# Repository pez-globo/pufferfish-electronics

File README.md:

# vent-pcb

Electronic hardware board layout files for the Pufferfish ventilator.

The schematic and PCB files for this project can be viewed online at [CADLAB.io](https://cadlab.io/project/22897).

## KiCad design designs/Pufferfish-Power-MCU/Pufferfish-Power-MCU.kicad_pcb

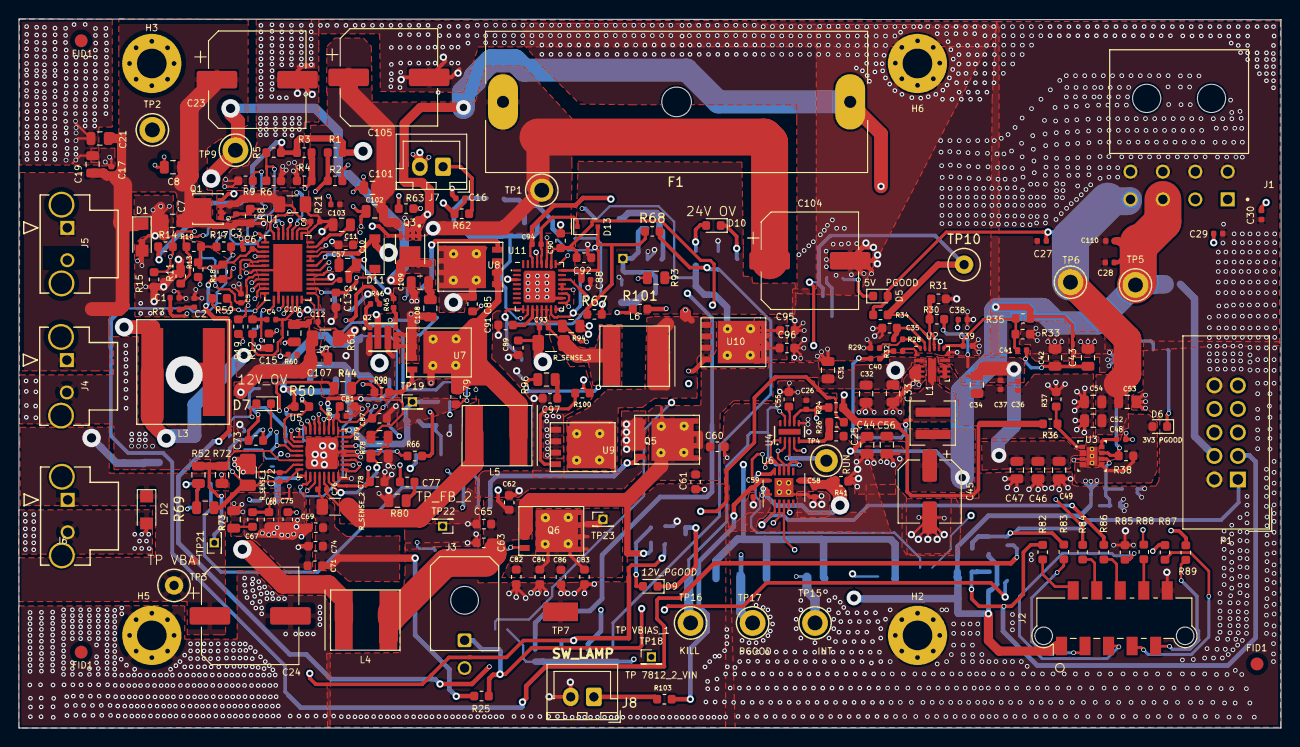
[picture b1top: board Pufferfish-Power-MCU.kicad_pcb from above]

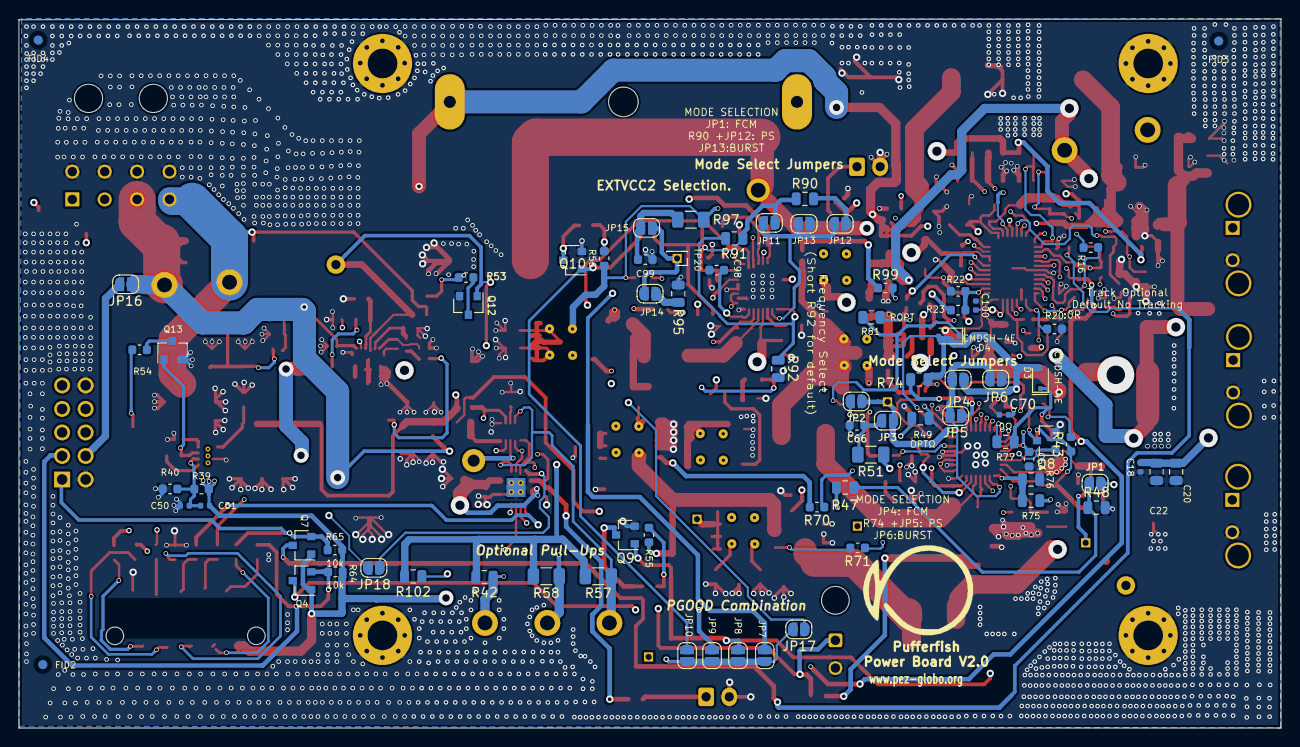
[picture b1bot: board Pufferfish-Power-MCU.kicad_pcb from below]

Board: 4 copper layers, 136.3 x 76.6 mm, 311 parts (77 on the bottom side), 148 nets.

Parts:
C1, C3, C16, C100: CAP_NC_0402; CAP_SMD_0402
C2, C26: CAP_10nF_50V_X7R_0402; CAP_SMD_0402
C4, C6, C17, C18, C27, C28, C29, C30, C36, C37, C40, C103, C110: CAP_100nF_50V_X7R_0402; CAP_SMD_0402
C5, C41, C51: CAP_100pF_10V_NP0_0402; CAP_SMD_0402
C7, C8, C19, C20, C21, C22, C34, C57, C101, C102, C106, C107, C108, C109: CAP_10uF_35V_X5R_0805; CAP_SMD_0805
C9, C12, C39, C50, C70, C72, C76, C88, C93, C94: CAP_1nF_50V_C0G_0402; CAP_SMD_0402
C10: CAP_1uF_35V_X7R_0603; CAP_SMD_0603
C11: CAP_330nF_35V_X7R_0805; CAP_SMD_0805
C13: CAP_470nF_35V_X7R_0603; CAP_SMD_0603
C14: CAP_2.2uF_10V_X7S_0402; CAP_SMD_0402
C15: CAP_330nF_16V_X7R_0603; CAP_SMD_0603
C23, C24, C104, C105: CAP_AE_SMD_220uF_25V_8mm; CP_Elec_10x7.9
C25, C64, C66, C75, C91: 0.1uF; CAP_SMD_0603
C31, C32, C33, C42, C43, C44, C46, C47, C49, C52, C53, C54, C56: CAP_22uF_25V_X5R_0805; CAP_SMD_0805
C35: CAP_4.7uF_16V_X6S_0603; CAP_SMD_0603
C38: CAP_47nF_50V_X7R_0402; CAP_SMD_0402
C45: CAP_AE_SMD_100uF_10V_6mm; CP_Elec_6.3x5.4
C48: CAP_3.3nF_50V_X7R_0402; CAP_SMD_0402
C55: 5.6u; CAP_SMD_0603
C58, C59: 0.1u; CAP_SMD_0402
C60: 150uF; CAP_SMD_0603
C61: 100uF; CAP_SMD_0603
C62: 4.7uF; CAP_SMD_0603
C63, C65: C_OPT; CAP_SMD_0603
C67: 2.2n; CAP_SMD_0603
C68: 68p; CAP_SMD_0603
C69: 33u; CAP_SMD_0603
C71, C74, C84, C85: 10u; CAP_SMD_0603
C73: 0.1u; CAP_SMD_0603
C77: 10n; CAP_SMD_0603
C78: 1n; CAP_SMD_0603
C79: 1nF; CAP_SMD_0603
C80: 0.1uF; CAP_SMD_0402
C81, C82, C92: OPT_CAP; CAP_SMD_0603
C83: 4.7u; CAP_SMD_0603
C86: 100u; CAP_SMD_0603
C87: 1u; CAP_SMD_0603
C89: 33uF; CAP_SMD_0603
C90: 10uF; CAP_SMD_0603
C95, C96, C97, C98, C99: CAP_SMD_0603
D1: TVS_24V_SOD123FL-2; D_SOD-123F
D2: TVS_15V_SOD123FL-2; D_SOD-123F
D3, D4, D13: CMDSH-4E; D_SOD-323F
D5, D6: LED_SMD_0603_ORANGE; LED_0603_1608Metric
D7, D9, D10: LED_SMD_0603_GREEN; LED_0603_1608Metric
D11: 1N4448HLP; D_SOD-123
F1: Fuse; Fuseholder_Cylinder-6.3x32mm_Schurter_0031-8002_Horizontal_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
FID1, FID1#2, FID1#3, FID2, FID3, FID4: Fiducial; Fiducial_1mm_Mask2mm
H2, H3, H5, H6: STANDOFF_ELECTRICAL; MountingHole_3.2mm_M3_Pad_Via
J1: 172316-1108; MOLEX_172316-1108
J2: 90814-0010; Molex_Picoflex_90814-0010_2x05_P1.27mm_Vertical
J3: 0430450200; Molex_Micro-Fit_3.0_43045-0200_2x01_P3.00mm_Horizontal
J4, J5, J6: CON_1722871202_MOL; UL_1722871202
J7: B2B-XH-A(LF)(SN); JST_XH_B2B-XH-A_1x02_P2.50mm_Vertical
J8: LAMP CONN; JST_XH_B2B-XH-A_1x02_P2.50mm_Vertical
JP1: SolderJumper_TRACKING; SolderJumper-2_P1.3mm_Open_RoundedPad1.0x1.5mm
JP2, JP14: SolderJumper_EXTMODE1; SolderJumper-2_P1.3mm_Open_RoundedPad1.0x1.5mm
JP3, JP15: SolderJumper_EXTMODE2; SolderJumper-2_P1.3mm_Open_RoundedPad1.0x1.5mm
JP4, JP11: SolderJumper_FCM; SolderJumper-2_P1.3mm_Open_RoundedPad1.0x1.5mm
JP5, JP12: SolderJumper_PS; SolderJumper-2_P1.3mm_Open_RoundedPad1.0x1.5mm
JP6, JP13: SolderJumper_Burst; SolderJumper-2_P1.3mm_Open_RoundedPad1.0x1.5mm
JP7, JP8, JP9, JP10, JP17, JP18: SolderJumper_PGOOD; SolderJumper-2_P1.3mm_Open_RoundedPad1.0x1.5mm
JP16: OPT_5V; SolderJumper-2_P1.3mm_Open_RoundedPad1.0x1.5mm
L1: PM2201.122NLT; L_Pulse_PA5001
L2: LOGO_PUFFERFISH
L3: XAL1010-103MEB; XAL1010
L4: 4.7u; L_Coilcraft_XxL7070
L5: 1.0u; L_Coilcraft_XxL7070
L6: 15uH; L_Coilcraft_XxL7070
P1: Aardvark Conn 10 P IDC; IDC-Header_2x05_P2.54mm_Vertical
Q1: FDMC8327L; TRANS_FDMC8327L
Q2: FDMC8030; TRANS_FDMC8030
Q3: SI7611DN-T1-GE3; VISHAY_SIS468DN-T1-GE3
Q4, Q7, Q8, Q9, Q10, Q12, Q13: 2N7002E; SOT-23
Q5, Q6: Q_NMOS_BSC093N04LSG; PG-TDSON-8
R1, R2, R4, R5, R9, R10, R11, R14, R15, R23: RES_0603_NC; RES_SMD_0603
R3, R6, R8, R13, R16, R17, R18, R20, R22, R31, R33, R34, R37, R38, R40, R59, R62: RES_10K_0603_SMD; RES_SMD_0603
R7, R32, R45, R46, R60: RES_0R_0402_SMD; RES_SMD_0402
R12: RES_301K_0603_SMD; RES_SMD_0603
R19: RES_100K_0603_SMD; RES_SMD_0603
R21, R61: CSNL1206FT3L00; RES_SMD_1206
R24: 1k; RES_SMD_0603
R25, R41, R64, R65: 10k; RES_SMD_0603
R26: 5.1k; RES_SMD_0603
R28: RES_62K_0402_SMD; RES_SMD_0402
R29: RES_51K_0402_SMD; RES_SMD_0402
R30: RES_47K_0603_SMD; RES_SMD_0603
R35, R36: RES_73K2_0603_SMD; RES_SMD_0603
R39: RES_31K6_0603_SMD; RES_SMD_0603
R42, R102: RPULL_OPT; RES_SMD_0805
R43, R55: 510R; RES_SMD_0603
R44, R69, R77: 0Ω; RES_SMD_0805
R47, R48, R49, R75, R76, R91, R92, R95: OPTΩ; RES_SMD_0805
R50, R66, R67, R68: 1M; RES_SMD_0603
R51, R97: OPTΩ; RES_SMD_1206
R52: 499k; RES_SMD_0805
R53: RES_330R_0603_SMD; RES_SMD_0603
R54: 330R; RES_SMD_0603
R56: 1.2k; RES_SMD_0603
R57, R58: RPULL_OPT; RES_SMD_1206
R63: RES_20K_0603_SMD; RES_SMD_0603
R70, R71, R82, R83, R84, R85, R86, R87, R88, R89, R98, R99, R100, R101: 0Ω; RES_SMD_0603
R72: 35.7k; RES_SMD_0805
R73: 15k; RES_SMD_0805
R74, R90: 100k OPT; RES_SMD_0805
R78: 49.9k; RES_SMD_0805
R79: 549K; RES_SMD_0805
R80: 3.6k; RES_SMD_0805
R81: ROPT; RES_SMD_0805
R93: 549k; RES_SMD_0805
R94: 28.7k; RES_SMD_0805
R96: 53.6k; RES_SMD_0805
R103: 150 Ω; RES_SMD_0603
R_SENSE_1: 0.003; RES_SMD_1206
R_SENSE_2: 0.004; RES_SMD_1206
R_SENSE_3: 0.015; RES_SMD_1206
TP1, TP2, TP3, TP4, TP5, TP6, TP9, TP15, TP16, TP17: TP_TH_KEYSTONE_5010; TestPoint_Keystone_5010-5014_Multipurpose
TP7: TP_SMT_KEYSTONE_5019; TP380X203
TP10: TP_PGOOD_5V; TestPoint_Keystone_5005-5009_Compact
TP18: TP_VOUT_12V; PinHeader_1x01_P1.27mm_Vertical
TP19: TP_EXTVCC1; PinHeader_1x01_P1.27mm_Vertical
TP20: TP_EXTVCC2; PinHeader_1x01_P1.27mm_Vertical
TP21: TP_VFB_1_1; PinHeader_1x01_P1.27mm_Vertical
TP22: TP_VFB_2_1; PinHeader_1x01_P1.27mm_Vertical
TP23: TP_VBIAS_1; PinHeader_1x01_P1.27mm_Vertical
U1: LTC4015EUHF#PBF; QFN50P700X500X80-39N
U2: TPS568215RNN; Texas_RNN0018A
U3: TPS82130; TPS82130SILR
U4: LTC2955; DFN-10-1EP_2x3mm_P0.5mm_EP0.64x2.4mm
U5: LTC7812; QFN-32-1EP_5x5mm_P0.5mm_EP3.45x3.45mm
U6: TXS0104ERGYR; Texas_S-PVQFN-N14_ThermalVias
U7, U8, U9, U10: BSC027N04LSG; PG-TDSON-8
U11: LTC7812-LTC7812; QFN-32-1EP_5x5mm_P0.5mm_EP3.45x3.45mm

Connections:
3V3-PGOOD: JP18.2, Q13.1, R38.2, U3.7
/3.3V Buck/3V3-EN: R36.2, R37.1, U3.1
/3.3V Buck/3V3-FB: C50.1, C51.2, R39.2, R40.1, U3.6
/3.3V Buck/3V3-SS: C48.1, U3.8
/5V Buck/5V-BUCK-BOOT: R32.1, U2.1
/5V Buck/5V-BUCK-SW: C40.1, L1.1, U2.6, U2.7
/5V Buck/5V-EN: R30.2, R31.1, U2.15
/5V Buck/5V-FB: C39.1, C41.2, R33.1, R35.2, U2.13
/5V Buck/5V-MODE: R28.2, R29.1, U2.18
/5V Buck/5V-SS: C38.1, U2.14
/LTC2955/INT_LVL: R42.1, TP15.1, U4.1, U6.12
/LTC2955/KILL_LVL: R57.1, TP16.1, U4.9, U6.10
/LTC2955/PG_LVL: R58.1, TP17.1, U4.2, U6.11
/LTC4015/PP-BATSENS: C100.1, R60.2, U1.18
/LTC4015/PP-BG: R45.2, U1.26
/LTC4015/PP-BOOST: C13.1, D11.1, U1.25
/LTC4015/PP-BOT-GATE: Q2.8, R45.1
/LTC4015/PP-CCREFM: C4.2, R12.2, U1.16
/LTC4015/PP-CCREFP: C4.1, R12.1, U1.17
/LTC4015/PP-CELL0: R1.1, R2.2, U1.38
/LTC4015/PP-CELL1: R3.2, R4.2, U1.1
/LTC4015/PP-CELL2: R5.1, R6.1, U1.2
/LTC4015/PP-CHEM0: R10.1, R11.2, U1.36
/LTC4015/PP-CHEM1: R14.1, R15.2, U1.37
/LTC4015/PP-CSP: C12.1, C15.1, C108.1, C109.1, L3.2, Q3.5, Q3.6, Q3.7, Q3.8, Q3.9, R61.1, TP9.1, U1.20
/LTC4015/PP-CSPM5: C15.2, U1.15
/LTC4015/PP-INFET-GATE: Q1.4, U1.34
/LTC4015/PP-MPPT: R22.1, R23.2, U1.21
/LTC4015/PP-NTC-BIAS: R59.1, U1.12
/LTC4015/PP-PMOS-GATE-CTRL: Q3.4, U1.29
/LTC4015/PP-RT: R19.1, U1.10
/LTC4015/PP-SENSE-CLN: C9.1, C10.1, C10.2, C11.1, C101.1, C102.1, C103.1, C104.1, C105.1, F1.2, R21.1, TP1.1, U1.31, U1.32
/LTC4015/PP-SENSE-CLP: C9.2, Q1.1, Q1.2, Q1.3, R21.2, U1.33
/LTC4015/PP-SW-NODE: C13.2, L3.1, Q2.4, Q2.9, U1.23
/LTC4015/PP-SYSM5: C11.2, U1.30
/LTC4015/PP-TG: R46.2, U1.24
/LTC4015/PP-TOP-GATE: Q2.1, R46.1
/LTC4015/PP-UVCLFB: C5.1, R16.1, U1.8
/LTC4015/PP-VC: C1.1, R7.1, U1.9
/LTC4015/VCCINT-PP-2V5: C14.1, U1.22
/LTC7812/BG_1_1: R70.1, U5.31
/LTC7812/BG_2_1: R98.2, U5.27
/LTC7812/BG_2_2: R100.2, U11.27
/LTC7812/BOOST_2_1: R81.1, U5.28
/LTC7812/BOOST_2_2: C94.2, D13.1, U11.28
/LTC7812/EXTVCC1: JP2.1, JP3.1, TP19.1, U5.25
/LTC7812/EXTVCC2: JP14.1, JP15.1, TP20.1, U11.25
/LTC7812/INTVCC_1: C70.1, C87.1, D3.2, D4.2, JP4.1, R50.1, R66.1, R74.1, R75.1, U5.24
/LTC7812/INTVCC_2: C88.1, D13.2, JP11.1, R67.1, R68.1, R90.1, R91.1, U11.24
/LTC7812/ITH_1_1: C67.1, C68.2, U5.5
/LTC7812/ITH_2_2: C98.2, R96.1, U11.15
/LTC7812/SW2_2: C94.1, L6.2, U9.5, U10.1, U10.2, U10.3, U11.30
/LTC7812/SW_2_1: C79.1, L5.2, U5.30, U7.5, U8.1, U8.2, U8.3
/LTC7812/TG_2_1: R99.2, U5.29
/LTC7812/TG_2_2: R101.1, U11.29
/LTC7812/TRACK_SS1_1: C64.1, JP1.2, U5.4
/LTC7812/VBIAS1: C80.1, C81.1, C82.1, C83.1, C84.1, C85.1, C86.1, Q6.5, R44.1, TP23.1, U5.26, U8.5
/LTC7812/VFB_1_1: R52.2, R72.1, TP21.1, U5.6
/LTC7812/VFB_2_2: R93.2, R94.1, U11.14
AAD_SCL: P1.1, Q7.2, R65.1, R83.2
AAD_SDA: P1.3, Q4.2, R64.1, R82.2
GND: C1.2, C2.2, C5.2, C6.1, C7.2, C8.2, C14.2, C16.2, C17.2, C18.2, C19.2, C20.2, C21.2, C22.2, C23.2, C24.2, C25.2, C26.2, C27.2, C28.2, C29.2, C30.2, C31.2, C32.2, C33.2, C34.2, C35.2, C36.2, C37.2, C38.2, C39.2, C42.2, C43.2, C44.2, C45.2, C46.2, C47.2, C48.2, C49.2, C50.2, C52.2, C53.2, C54.2, C55.1, C56.2, C57.2, C58.2, C59.2, C60.2, C61.2, C62.2, C63.2, C64.2, C65.2, C66.2, C68.1, C69.2, C70.2, C71.2, C74.2, C75.2, C78.1, C80.2, C81.2, C82.2, C83.2, C84.2, C85.2, C86.2, C87.2, C88.2, C89.2, C90.2, C91.2, C92.2, C95.2, C96.2, C97.1, C98.1, C99.2, C100.2, C101.2, C102.2, C103.2, C104.2, C105.2, C106.2, C107.2, C108.2, C109.2, C110.2, D1.2, D2.2, H2.1, H3.1, H5.1, H6.1, J1.5, J1.6, J1.7, J1.8, J2.10, J3.2, J4.2, J5.2, J6.2, J7.2, J8.2, JP6.1, JP13.1, P1.2, P1.10, Q2.5, Q5.1, Q5.2, Q5.3, Q8.2, Q9.2, Q10.2, Q12.2, Q13.2, R2.1, R4.1, R6.2, R9.1, R11.1, R15.1, R19.2, R20.2, R22.2, R29.2, R31.2, R33.2, R37.2, R40.2, R41.1, R48.2, R49.2, R63.2, R72.2, R73.2, R76.2, R78.1, R80.2, R85.2, R92.2, R94.2, R95.2, TP7.1, U1.7, U1.14, U1.39, U2.3, U2.4, U2.5, U2.8, U2.9, U2.10, U2.12, U3.3, U3.9, U4.6, U4.10, U5.16, U5.18, U5.20, U5.21, U5.33, U6.7, U6.15, U7.1, U7.2, U7.3, U9.1, U9.2, U9.3, U11.16, U11.18, U11.20, U11.21, U11.33
INTCON_WALL: C3.1, C7.1, C8.1, C17.1, C19.1, C21.1, C23.1, D1.1, J4.1, J5.1, Q1.5, Q1.6, Q1.7, Q1.8, Q1.9, R8.1, TP2.1, U1.35
LTC2955_PGD: R89.2, U6.4
LTC2955_SHDN_INT: R87.2, U6.3
LTC2955_nKILL: R88.2, U6.5
LTC4015_INTVCC: C6.2, C57.1, D11.2, R1.2, R3.1, R5.2, R10.2, R13.1, R14.2, R17.1, R18.1, R23.1, R42.2, R57.2, R58.2, R102.2, U1.3, U1.27, U1.28
LTC7812_PG: R86.2, U6.2
LTC7812_RUN: R102.1, TP4.1, U4.3, U5.17, U5.19, U11.17, U11.19
NTC-SENSE-INPUT: C16.1, R59.2, R62.1, R63.1, U1.11
unnamed: C2.1, R7.2
unnamed: C3.2, R8.2, R9.2, R16.2
unnamed: C25.1, R26.2, U4.5
unnamed: C26.1, R24.1, U4.4, U4.7
unnamed: C40.2, R32.2
unnamed: C55.2, U4.8
unnamed: C66.1, JP3.2, R51.2
unnamed: C67.2, R73.1
unnamed: C72.2, L4.2, R_SENSE_1.1, U5.7
unnamed: C73.1, D3.1, R77.1
unnamed: C75.1, U5.11
unnamed: C76.1, L5.1, R_SENSE_2.1, U5.13
unnamed: C77.1, C78.2, U5.15
unnamed: C77.2, R80.1
unnamed: C79.2, D4.1, R81.2
unnamed: C91.1, U11.11
unnamed: C93.1, L6.1, R_SENSE_3.1, U11.13
unnamed: C97.2, R96.2
unnamed: C99.1, JP15.2, R97.2
unnamed: D5.1, R53.1
unnamed: D6.1, R54.1
unnamed: D7.1, Q8.3
unnamed: D7.2, R43.2
unnamed: D9.1, Q9.3
unnamed: D9.2, R55.2
unnamed: D10.1, Q10.3
unnamed: D10.2, R56.2
unnamed: J2.2, R82.1
unnamed: J2.3, R83.1
unnamed: J2.4, R84.1
unnamed: J2.5, R85.1
unnamed: J2.6, R86.1
unnamed: J2.7, R87.1
unnamed: J2.8, R88.1
unnamed: J2.9, R89.1
unnamed: J3.1, R25.1, R26.1
unnamed: J7.1, R62.2
unnamed: J8.1, R103.2
unnamed: JP1.1, R47.2, R48.1
unnamed: JP2.2, R49.1
unnamed: JP4.2, JP5.2, JP6.2, U5.10
unnamed: JP5.1, R74.2
unnamed: JP11.2, JP12.2, JP13.2, U11.10
unnamed: JP12.1, R90.2
unnamed: JP14.2, R95.1
unnamed: JP16.2, P1.4
unnamed: Q5.4, R70.2
unnamed: Q6.4, R71.2
unnamed: Q12.3, R53.2
unnamed: Q13.3, R54.2
unnamed: R44.2, R79.1
unnamed: R52.1, R69.2
unnamed: R71.1, U5.2
unnamed: R75.2, R76.1, U5.9
unnamed: R77.2, U5.32
unnamed: R78.2, R79.2, TP22.1, U5.14
unnamed: R91.2, R92.1, U11.9
unnamed: R98.1, U7.4
unnamed: R99.1, U8.4
unnamed: R100.1, U9.4
unnamed: R101.2, U10.4
OV_12V: JP9.2, Q8.1, R66.2, U5.22
OV_24V: JP10.2, Q10.1, R68.2, U11.22
PGOOD_12V: JP8.1, Q9.1, R50.2, U5.3
PGOOD_24V: JP7.1, R67.2, U11.3
PGOOD_COMB: JP7.2, JP8.2, JP9.1, JP10.1, JP17.2, JP18.1, U6.13
PP-EQ-EN: R20.1, U1.13
PP-SCL: Q7.3, R17.2, U1.4
PP-SDA: Q4.3, R13.2, U1.5
PP-SMB-nALERT: R18.2, R84.2, U1.6
VBAT-IN-12V: C12.2, C18.1, C20.1, C22.1, C24.1, C106.1, C107.1, D2.1, J6.1, R60.1, R61.2, TP3.1, U1.19
VBUCK-INT-5V: C35.1, R28.1, U2.17
VIN_7812_1_RAW: C69.1, C71.1, C74.1, C76.2, F1.1, Q2.10, Q3.1, Q3.2, Q3.3, R24.2, R25.2, R36.1, R_SENSE_2.2, U5.12
VIN_7812_2: C29.1, C31.1, C32.1, C33.1, C34.1, C36.1, C37.1, C46.1, C47.1, C49.1, C60.1, C61.1, C62.1, C63.1, C65.1, C72.1, C73.2, C89.1, C90.1, C92.1, C93.2, J1.2, L4.1, Q5.5, Q6.1, Q6.2, Q6.3, R30.1, R43.1, R51.1, R55.1, R69.1, R_SENSE_1.2, R_SENSE_3.2, TP18.1, U2.2, U2.11, U3.2, U5.1, U5.8, U11.12, U11.26
VOUT_7812_24V: C30.1, C95.1, C96.1, J1.1, R47.1, R56.1, R93.1, R97.1, U10.5
VSYS-3V3: C27.1, C51.1, C52.1, C53.1, C54.1, C58.1, D5.2, D6.2, J1.4, J2.1, Q4.1, Q7.1, R34.1, R38.1, R39.1, R41.2, R64.2, R65.2, TP6.1, U3.4, U3.5, U6.1, U6.8
VSYS-5V0: C28.1, C41.1, C42.1, C43.1, C44.1, C45.1, C56.1, C59.1, C110.1, J1.3, JP16.1, L1.2, R35.1, R103.1, TP5.1, U6.14
VSYS-5V0-PGOOD: JP17.1, Q12.1, R34.2, TP10.1, U2.16

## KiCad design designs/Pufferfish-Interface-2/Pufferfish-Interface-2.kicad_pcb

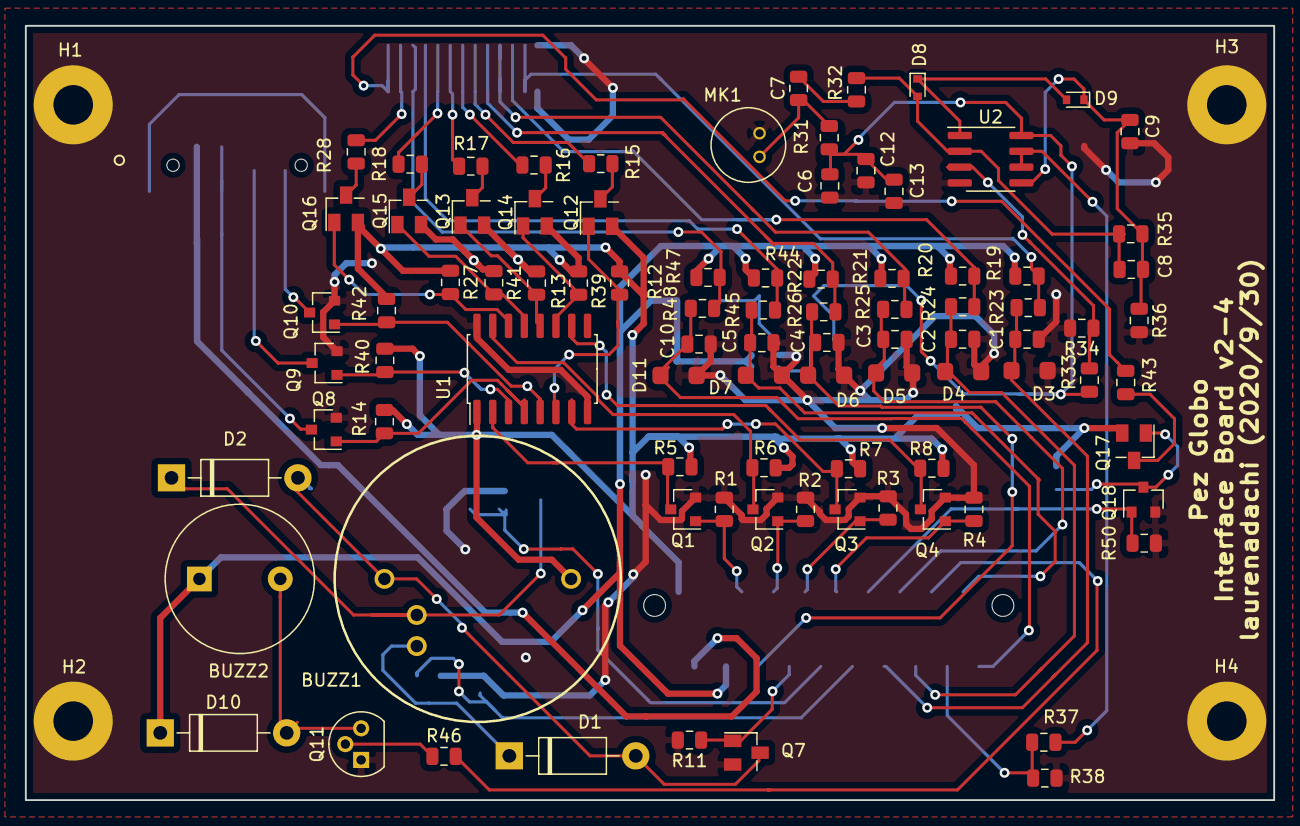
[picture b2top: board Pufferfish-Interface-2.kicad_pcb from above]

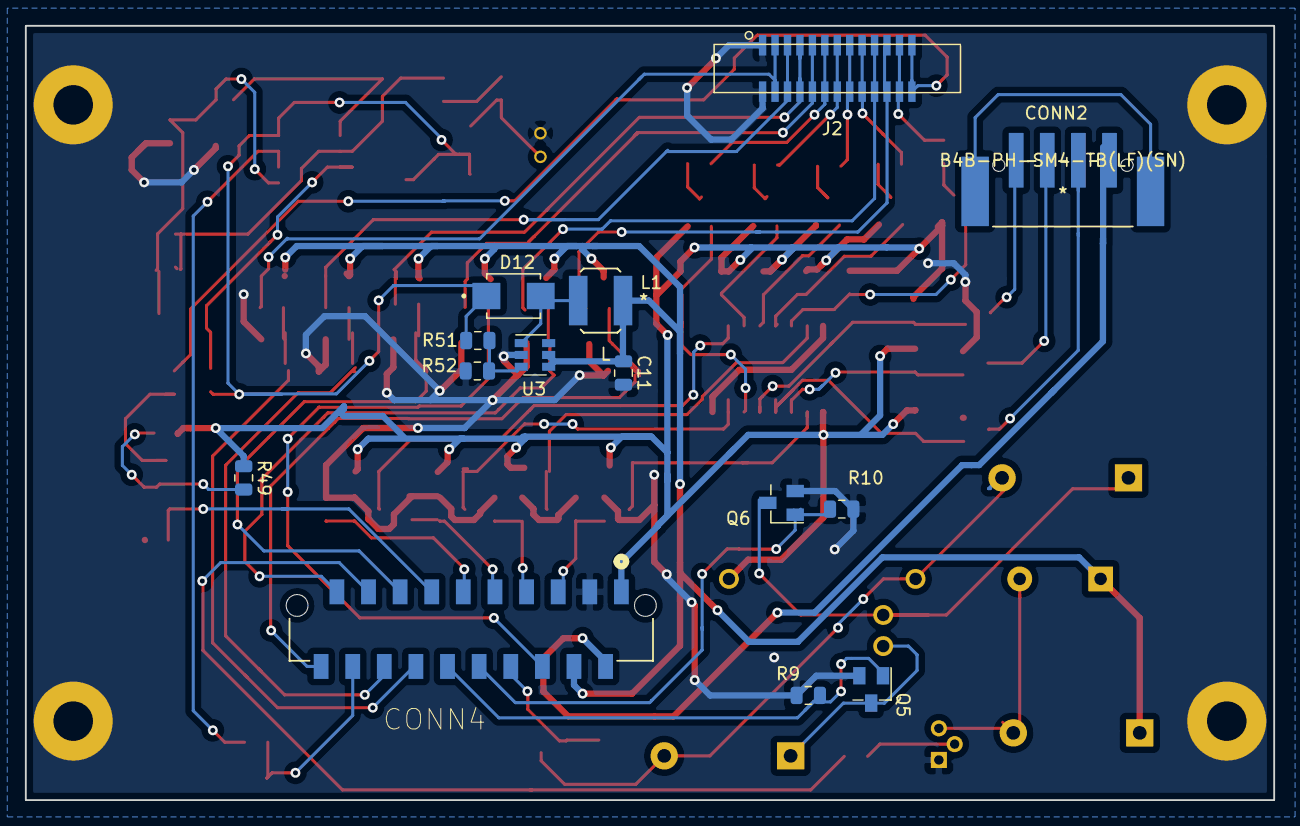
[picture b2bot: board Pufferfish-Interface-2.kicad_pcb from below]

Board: 2 copper layers, 100.3 x 62.2 mm, 107 parts (14 on the bottom side), 70 nets.

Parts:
BUZZ1: BUZZER-MALLORY; Buzzer-MSS5MMG
BUZZ2: BUZZER; Buzzer-CUI_CSQG703BP
C1, C2, C3, C4, C5, C10: 0.1uF; CAP_SMD_0805
C6, C13: 100nF; CAP_SMD_0805
C7, C9, C11, C12: 10uF; CAP_SMD_0805
C8: 100pF; CAP_SMD_0805
CONN2: B4B-PH-SM4-TB(LF)(SN); 1778719
CONN4: 5103308-5; MOLEX_90814-0920
D1, D2, D10: 1N4001; D_DO-41_SOD81_P10.16mm_Horizontal
D3, D4, D5, D6, D7, D11: SMF3.3; D_TVS_SMF3.3
D8, D9: 1N4148WT; D_SOD-523
D12: D_Schottky; DIOM5436X247N
H1, H2, H3, H4: STANDOFF_ELECTRICAL; STANDOFF-ELECTRICAL-NOTHERMALS
J2: Conn_01x13_Male; 0526101333
L1: L; NRS5030T4R7MMGJV
MK1: Microphone; Microphone-EM-6022P
Q1, Q2, Q3, Q4, Q8, Q9, Q10, Q18: 2N7002E; SOT-23
Q5, Q6, Q7: FDN337N; SuperSOT-3
Q11: PN2222ABU; TO-92
Q12, Q13, Q14, Q15, Q16, Q17: Q_PMOS_GSD; SuperSOT-3
R1, R2, R3, R4, R5, R6, R7, R8, R9, R10, R11, R12, R13, R14, R15, R16, R17, R18, R19, R20, R21, R22, R23, R24, R25, R26, R27, R28, R31, R32, R33, R34, R35, R36, R37, R38, R39, R40, R41, R42, R43, R44, R45, R46, R47, R48, R49, R50, R51, R52: RES_SMD_0805
U1: STPIC6D595; SO-16_5.3x10.2mm_P1.27mm
U2: TL072; SOIC-8_3.9x4.9mm_P1.27mm
U3: SB6286; SOT-23-6

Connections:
3.3V: BUZZ2.1, C11.1, CONN4.4, D10.1, L1.1, R19.1, R20.1, R21.1, R22.1, R44.1, R47.1, U3.4, U3.5
5V: BUZZ1.1, CONN4.1, Q12.2, Q13.2, Q14.2, Q15.2, Q16.2, Q17.2, R5.1, R6.1, R7.1, R8.1, R12.1, R13.1, R14.1, R27.1, R39.1, R40.1, R41.1, R42.1, R49.1, U1.1
+12V: CONN2.1, CONN4.2
ALARM1_HIGH: CONN4.12, Q5.1, R9.1
ALARM1_LOW: CONN4.8, Q7.1, R11.1
ALARM1_MED: CONN4.10, Q6.1, R10.1
ALARM1_SENSE: CONN4.18, R37.2, R38.1
ALARM2_EN: CONN4.17, R46.2
DRAIN0: Q9.1, R40.2, U1.3
DRAIN1: Q8.1, R14.2, U1.4
DRAIN2: Q10.1, R42.2, U1.5
DRAIN3: Q12.1, R12.2, U1.6
DRAIN4: Q14.1, R39.2, U1.11
DRAIN5: Q13.1, R13.2, U1.12
DRAIN6: Q15.1, R41.2, U1.13
DRAIN7: Q16.1, R27.2, U1.14
GND: C1.2, C2.2, C3.2, C4.2, C5.2, C6.2, C9.2, C10.2, C11.2, C12.2, C13.2, CONN4.3, D3.2, D4.2, D5.2, D6.2, D7.2, D11.2, H1.P1, H2.P1, H3.P1, H4.P1, J2.1, MK1.1, Q1.2, Q2.2, Q3.2, Q4.2, Q5.2, Q6.2, Q7.2, Q8.2, Q9.2, Q10.2, Q11.1, Q18.2, R1.2, R2.2, R3.2, R4.2, R9.2, R10.2, R11.2, R34.2, R36.2, R38.2, R50.2, R52.2, U1.8, U1.16, U2.4, U3.2
MK_PWR: C6.1, C12.1, C13.1, D12.1, R31.1, R33.1, R51.1, U2.8
unnamed: BUZZ1.2, D1.1, Q5.3
unnamed: BUZZ1.3, D2.1, Q6.3
unnamed: BUZZ1.4, D1.2, D2.2, Q7.3
unnamed: BUZZ2.2, D10.2, Q11.3
unnamed: C7.1, MK1.2, R31.2
unnamed: C7.2, R32.1
unnamed: C8.1, C9.1, D9.1, R35.2, R36.1, U2.5
unnamed: C8.2, D8.2, R32.2, R35.1, U2.2
unnamed: CONN2.2, Q8.3
unnamed: CONN2.3, Q9.3
unnamed: CONN2.4, Q10.3
unnamed: CONN2.5, CONN2.6
unnamed: D8.1, D9.2, U2.1
unnamed: D12.2, L1.2, U3.1
unnamed: J2.6, R15.1
unnamed: J2.7, R16.1
unnamed: J2.8, R17.1
unnamed: J2.9, R18.1
unnamed: J2.12, R28.1
unnamed: J2.13, R43.1
unnamed: Q1.3, R5.2, U1.2
unnamed: Q2.3, R6.2, U1.15
unnamed: Q3.3, R7.2, U1.7
unnamed: Q4.3, R8.2, U1.10
unnamed: Q11.2, R46.1
unnamed: Q17.1, Q18.3, R49.2
unnamed: R33.2, R34.1, U2.3
unnamed: R37.1, U2.6, U2.7
unnamed: R51.2, R52.1, U3.3
SER_CLR: CONN4.9, Q3.1, R3.1
SET_100_O2: C2.1, CONN4.16, D4.1, R24.2
SET_ALARM_EN: C1.1, CONN4.14, D3.1, R23.2
SET_LOCK: C4.1, CONN4.6, D6.1, R26.2
SET_MANUAL_BREATH: C3.1, CONN4.15, D5.1, R25.2
SET_NEBULIZATION: C5.1, CONN4.19, D7.1, R45.2
SET_WINDOW: C10.1, CONN4.20, D11.1, R48.2
SW1_EN: J2.2, R19.2, R23.1
SW1_LED: Q12.3, R15.2
SW2_EN: J2.3, R20.2, R24.1
SW2_LED: Q14.3, R16.2
SW3_EN: J2.4, R21.2, R25.1
SW3_LED: Q13.3, R17.2
SW4_EN: J2.5, R22.2, R26.1
SW4_LED: Q15.3, R18.2
SW5_EN: J2.10, R44.2, R45.1
SW5_LED: Q16.3, R28.2
SW6_EN: J2.11, R47.2, R48.1
SW6_LED: Q17.3, R43.2
SW6_LED_CNTRL: CONN4.13, Q18.1, R50.1
~SER_CLK: CONN4.7, Q2.1, R2.1
~SER_IN: CONN4.5, Q1.1, R1.1
~SER_RCLK: CONN4.11, Q4.1, R4.1

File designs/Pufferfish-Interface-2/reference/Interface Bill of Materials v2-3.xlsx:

Image |  | Unique ID | Status | Manufacturer or Distributor | Part # | Description of Part | Qty | Description of Location | Notes | Added By | Contact/Order link |  | Qty ordered | Date ordered | Status |  | B - Buzzer/Speaker
ELECTRICAL - INTERFACE BOARD |  |  |  |  |  |  |  |  |  |  |  |  |  |  |  |  | C - Capacitor
 | BUZZ1 |  |  | Mallory Sonalert Products Inc (Digikey) | MSS5MMV | Regulatory buzzer | 1 |  |  |  | https://www.digikey.com/product-detail/en/mallory-sonalert-p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
 | BUZZ2 |  |  | CUI Devices | CSQG703BP | Technical buzzer | 1 |  |  |  | https://www.digikey.com/product-detail/en/cui-devices/CSQG70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
 | C1-5, 10 |  |  | Kemet |  | 0.1uF | 6 | 805 |  |  | https://www.digikey.com/product-detail/en/kemet/C0805C104Z5V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
 | C6 |  |  | Kemet |  | 100nF | 1 | 805 |  |  | https://www.digikey.com/product-detail/en/kemet/C0805C104Z5V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
 | C7,9 |  |  | Kemet |  | 10uF | 2 | 805 |  |  | https://www.digikey.com/product-detail/en/kemet/C0805C106K8P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
 | C8 |  |  | Kemet |  | 100pF | 1 | 805 |  |  | https://www.digikey.com/product-detail/en/kemet/C0805C101JAG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
 | CONN2 |  |  | Pheonix Contact | 1778719 | LED connector | 1 |  | Updated |  | https://www.digikey.com/product-detail/en/phoenix-contact/17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
 | CONN4 |  |  | Molex | 908140920 | Connector to Control Board | 1 |  | Updated |  | https://www.digikey.com/product-detail/en/0908140920/WM3966C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
 | D1,2,10 |  |  | ON Semiconductor (Digikey) | 1N4001 | High Current Medical Alarm Diodes | 3 |  |  |  | https://www.digikey.com/product-detail/en/on-semiconductor/1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
 | D3,4,5,6,7,11 |  |  | Littelfuse Inc (Digikey) | SMF3.3 | ESD Diode | 6 |  |  |  | https://www.digikey.com/product-detail/en/littelfuse-inc/SMF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
 | D8,9 |  |  | ON Semiconductor (Digikey) | 1N4148WT | Standard Diode | 2 |  |  |  | https://www.digikey.com/product-detail/en/on-semiconductor/1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
 | J2 |  |  | Molex | 526101333 | Connector to Membrane buttons | 1 |  | Updated |  | https://www.digikey.com/product-detail/en/molex/0526101333/W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
 | MK1 |  |  | Soberton Inc | EM-6022P | Microphone | 1 |  |  |  | https://www.digikey.com/product-detail/en/soberton-inc/EM-60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
 | Q1,2,3,4,8,9,10,18 |  |  | Vishay Siliconix (Digikey) | 2N7002E-T1-E3 | MOSFETs | 8 |  |  |  | https://www.digikey.com/product-detail/en/vishay-siliconix/2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
 | Q5,6,7 |  |  | ON Semiconductor (Digikey) | FDN337N | MOSFETs (Medical Alarm) | 3 |  |  |  | https://www.digikey.com/product-detail/en/on-semiconductor/F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
 | Q11 |  |  | Fairchild Semiconductor | PN2222ABU | BJT (BUZZ2) | 1 |  |  |  | https://www.digikey.com/product-detail/en/fairchild-semicond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
 | Q12,13,14,15,16,17 |  |  | ON Semiconductor (Digikey) | FDN352AP | PMOS | 6 |  |  |  | https://www.digikey.com/product-detail/en/on-semiconductor/F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
R1-50 | R1-14, R19-R27, R31, R39-42, R44-45, R47-50 |  |  | Yageo |  | 10K | 34 | 805 |  |  | https://www.digikey.com/product-detail/en/RC0805FR-0710KL/31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
 | R46 |  |  | TE Connectivity Passive Product |  | 180 | 1 | 805 |  |  | https://www.digikey.com/product-detail/en/te-connectivity-pa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
 | R15-18, R28,R43 |  |  | Panasonic Electronic Components |  | 85 | 6 | 805 |  |  | https://www.digikey.com/product-detail/en/ERJ-6GEYJ820V/P82A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
 | R29 |  |  | Vishay Dale |  | 820 | 1 | 805 |  |  | https://www.digikey.com/product-detail/en/vishay-dale/CRCW08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
 | R30 |  |  | TE Connectivity Passive Product |  | 1.5K | 1 | 805 |  |  | https://www.digikey.com/product-detail/en/te-connectivity-pa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
 | R32 |  |  | TE Connectivity Passive Product |  | 2.2K | 1 | 805 |  |  | https://www.digikey.com/product-detail/en/te-connectivity-pa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
 | R34,36 |  |  | Yageo |  | 100K | 2 | 805 |  |  | https://www.digikey.com/product-detail/en/yageo/RC0805FR-071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
 | R35 |  |  | TE Connectivity Passive Product |  | 820K | 1 | 805 |  |  | https://www.digikey.com/product-detail/en/te-connectivity-pa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
 | R37 |  |  | TE Connectivity Passive Product |  | 3.9K | 1 | 805 |  |  | https://www.digikey.com/product-detail/en/te-connectivity-pa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
 | R38 |  |  | Panasonic Electronic Components |  | 3.6K | 1 | 805 |  |  | https://www.digikey.com/product-detail/en/panasonic-electron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
 | R33 |  |  | TE Connectivity Passive Product |  | 220K | 1 | 805 |  |  | https://www.digikey.com/product-detail/en/te-connectivity-pa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
 | U1 |  |  | STMicroelectronics | STPIC6D595MTR | Barrel Shifter | 1 |  |  |  | https://www.digikey.com/product-detail/en/stmicroelectronics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
 | U2 |  |  | STMicroelectronics | TL072CDT | Op Amps | 1 |  |  |  | https://www.digikey.com/product-detail/en/stmicroelectronics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
Non PCB Parts
 | CONN |  |  | TE Connectivity AMP Connectors | 1658620-4 | F adapter to control board | 1 |  |  |  | https://www.digikey.com/product-detail/en/te-connectivity-am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
 | CONN |  |  | TE Connectivity AMP Connectors | A3AAH-2006G | F Cable to control board | 1 |  |  |  | https://www.digikey.com/product-detail/en/te-connectivity-am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
 | CONN |  |  | JST Sales America | PHR-4 | JST F | 1 |  |  |  | https://www.digikey.com/product-detail/en/jst-sales-america-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
 | CONN |  |  | JST Sales America | SPH-004T-P0.5S | JST F to LED strip | 1 |  |  |  | https://www.digikey.com/product-detail/en/jst-sales-america-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
 | D |  |  | Inspired LED LLC | 12V-SB-RGB-5M | LED strip | 1 |  |  |  | https://www.digikey.com/product-detail/en/inspired-led-llc/1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
 | SW |  |  | JR Panel | JR Panel Custom | Membrane switches | 1 |  |  |  | https://www.jrpanel.com/switch/buy?Width=10&Height=10&Num=4&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
 | L1 |  |  | Taiyo-Yuden | NRS5030T4R7MMGJV | 4.7 uH +-20% | 1 |  | New |  | https://www.digikey.com/product-detail/en/taiyo-yuden/NRS503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
 | R51 |  |  | Yageo | RC0805FR-07360KL | 360K | 1 |  | New |  | https://www.digikey.com/product-detail/en/yageo/RC0805FR-073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
 | R52 |  |  | Panasonic Electronic Components | ERJ-6ENF3002V | 30K | 1 |  | New |  | https://www.digikey.com/product-detail/en/panasonic-electron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
 | U3 |  |  | SHOUDING | SB6286 |  | 1 |  | New |  | https://lcsc.com/product-detail/DC-DC-Converters_SB6286_C157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
 | D11 |  |  | ON Semiconductor | SS22T3G |  | 1 |  | New |  | https://www.digikey.com/product-detail/en/on-semiconductor/S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
 | C11,12 |  |  | Kemet |  | 10 uF | 2 |  | New |  | https://www.digikey.com/product-detail/en/kemet/C0805C106K8P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
 | C13 |  |  | Kemet |  | 100 nF | 1 |  | New |  | https://www.digikey.com/product-detail/en/kemet/C0805C104Z5V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

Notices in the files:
parts and their libraries:
Copyright 2016 Accelerated Designs. All rights reserved.
